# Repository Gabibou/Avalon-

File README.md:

# 🚀 Avalon

Welcome to the **Avalon Project** GitHub page!

Avalon is an open-source autonomous UAV (Unmanned Aerial Vehicle) project started in **January 2023** by two electrical engineering students passionate about aerospace, embedded systems, and autonomous flight systems.

At first, we planned to build a rocket 🚀  
But since many people were already working on similar projects, we decided to take on a different challenge:

> ✈️ Designing and building a fully autonomous flying wing.

The objective of Avalon is to develop both the **hardware** and the **software** required for a low-cost, repairable, and self-flying UAV platform.

The project combines multiple engineering fields, including:

- Embedded systems
- Electronics design
- Aerodynamics
- Autonomous navigation
- Telemetry and communication
- Power management

Avalon is also a long-term learning project that allows us to experiment, improve our skills, and progressively build more advanced autonomous flight systems.

---

# 🧩 Control Board Philosophy

The Avalon control board was designed to be flexible and reusable across multiple types of autonomous vehicles.

The main objective is to support both:

- ✈️ **2-axis flying wings and aircraft**
- 🚀 **3-axis rockets and experimental vehicles**

By keeping the hardware architecture modular, the same board can be adapted to different flight configurations with only software and parameter changes.

---

# 🔌 Communication & Control Interface

The board exposes its internal configuration and control system through a **register-based interface** accessible over USB communication.

This approach allows a computer or ground station software to:

- 📊 Read real-time telemetry values
- ⚙️ Configure onboard parameters
- 🎮 Manually control the vehicle
- 💾 Upload autonomous flight settings
- 🧪 Debug and test peripherals
- 🚀 Enable autonomous flight modes

The communication system behaves similarly to a memory-mapped register interface commonly found in embedded systems.

Each register corresponds to a specific feature or data field, such as:

- REVISION_STATUS
- SYSTEM_STATUS
- PID_CONTROL
- COMMAND
- SENSOR_CONFIG
- DEBUG
- ACTUATOR_CONFIG
- FLIGHT_CONTROL
- ALERTS
- MEMORY_CONTROL

This architecture provides a simple and scalable way to interact with the firmware while remaining hardware-independent.

---

# 📌 Roadmap

> 🚧 This section will be completed later.

---

# 🧠 Project Architecture

The project is organized into multiple folders, each with a dedicated role:

```text
Avalon/
├── mx/            # STM32CubeMX generated peripheral configuration
├── lib/           # External libraries imported using git submodules
├── test/          # Sanity and validation tests executed before commits
├── platformio/    # PlatformIO extension configuration files
├── src/           # Main firmware source files
├── inc/           # Header files and firmware interfaces
```

## 📂 Folder Details

### `mx/`

Contains STM32 peripheral configuration generated using:

- 🧩 STM32CubeMX
- ⚙️ STM32CubeIDE

This folder is mainly used to generate initialization code for peripherals such as:

- UART
- SPI
- I2C
- Timers
- DMA
- GPIO
- etc.

---

### `lib/`

Contains external dependencies and libraries imported using **Git submodules**.

This allows the project to:

- keep dependencies separated,
- simplify updates,
- and maintain cleaner firmware code.

---

### `test/`

Contains all sanity tests and validation routines that should pass before committing changes.

These tests help ensure:

- firmware stability,
- hardware reliability,
- and regression prevention.

---

### `platformio/`

Contains the configuration files used by the **PlatformIO** extension.

PlatformIO is used for:

- project building,
- dependency management,
- flashing,
- and debugging.

---

### `src/` and `inc/`

Main firmware source and header files.

These folders contain:

- flight logic,
- drivers,
- telemetry,
- navigation,
- control algorithms,
- and all embedded application code.

---

# 🛠️ First Prototype Overview

The first prototype is based on a custom board using the:

- 🧠 STM32G474RET6 MCU

It integrates:

- 📌 BNO055 IMU
- 🌡️ BMP390 barometric pressure sensor
- 📍 L80 GPS module
- 📡 Wio-E5 telemetry module
- 🔋 Current and battery voltage monitoring
- ⚡ Additional onboard peripherals

For the aircraft itself, we decided to use a **3D printed flying wing** in order to focus first on hardware and software validation.

The selected model is:

> ✈️ **EBW-160** from Eclipson

The aircraft has a wingspan of **160 cm (5.2 ft)**, making it a fairly large platform.

## 🧱 Materials

### First prototype

- Printed using standard PLA
- Lower cost and easier to replace during testing

### Future prototype

- Planned in LW-PLA (Lightweight PLA)
- Reduced weight for improved flight performance

# 📸 Prototype V1

---

# ✈️ Second Prototype Overview

---

# 📦 Cloning the Project

This project uses **Git submodules** for external libraries.

Because of this, cloning the repository normally is **not enough** ❌

You must clone the repository recursively to automatically download all dependencies.

## ✅ Recommended Clone Command

```bash
git clone --recurse-submodules https://github.com/Gabibou/Avalon-.git
```

---

## 🔄 Updating Submodules

If you already cloned the repository without submodules, run:

```bash
git submodule update --init --recursive
```

To update all submodules later:

```bash
git submodule update --remote --recursive
```

---

# 📜 License

This project is distributed under the MIT License.

📄 [MIT License](https://choosealicense.com/licenses/mit/)

---

# 🙌 Acknowledgements

Special thanks to:

- 🌱 [Seeed Studio](https://www.seeedstudio.com/) for their partnership and support.

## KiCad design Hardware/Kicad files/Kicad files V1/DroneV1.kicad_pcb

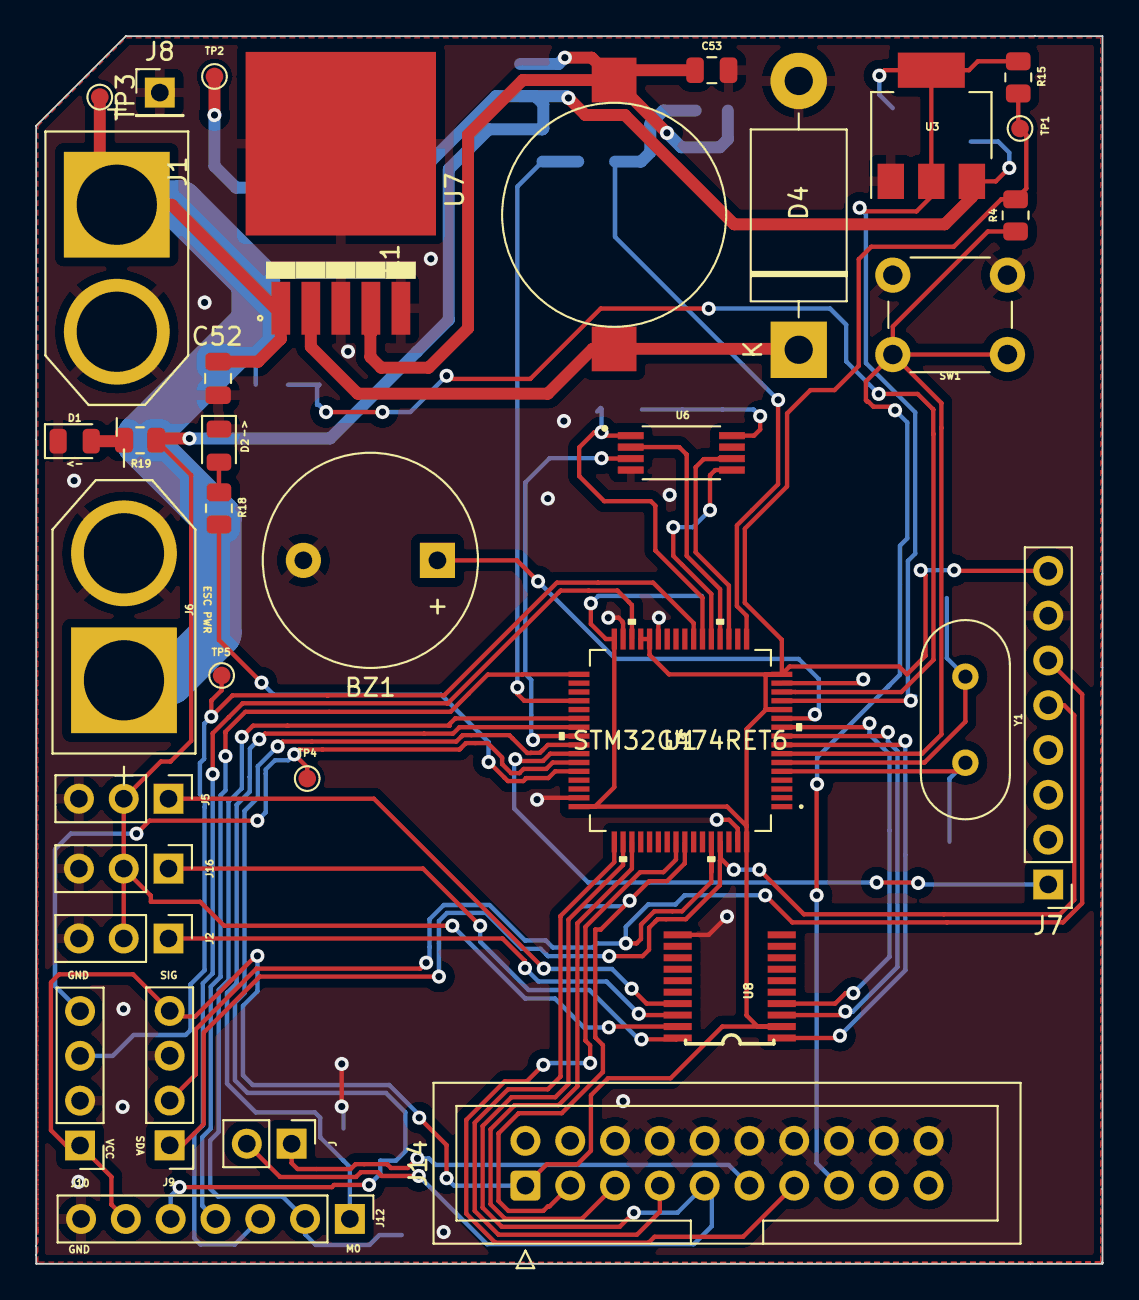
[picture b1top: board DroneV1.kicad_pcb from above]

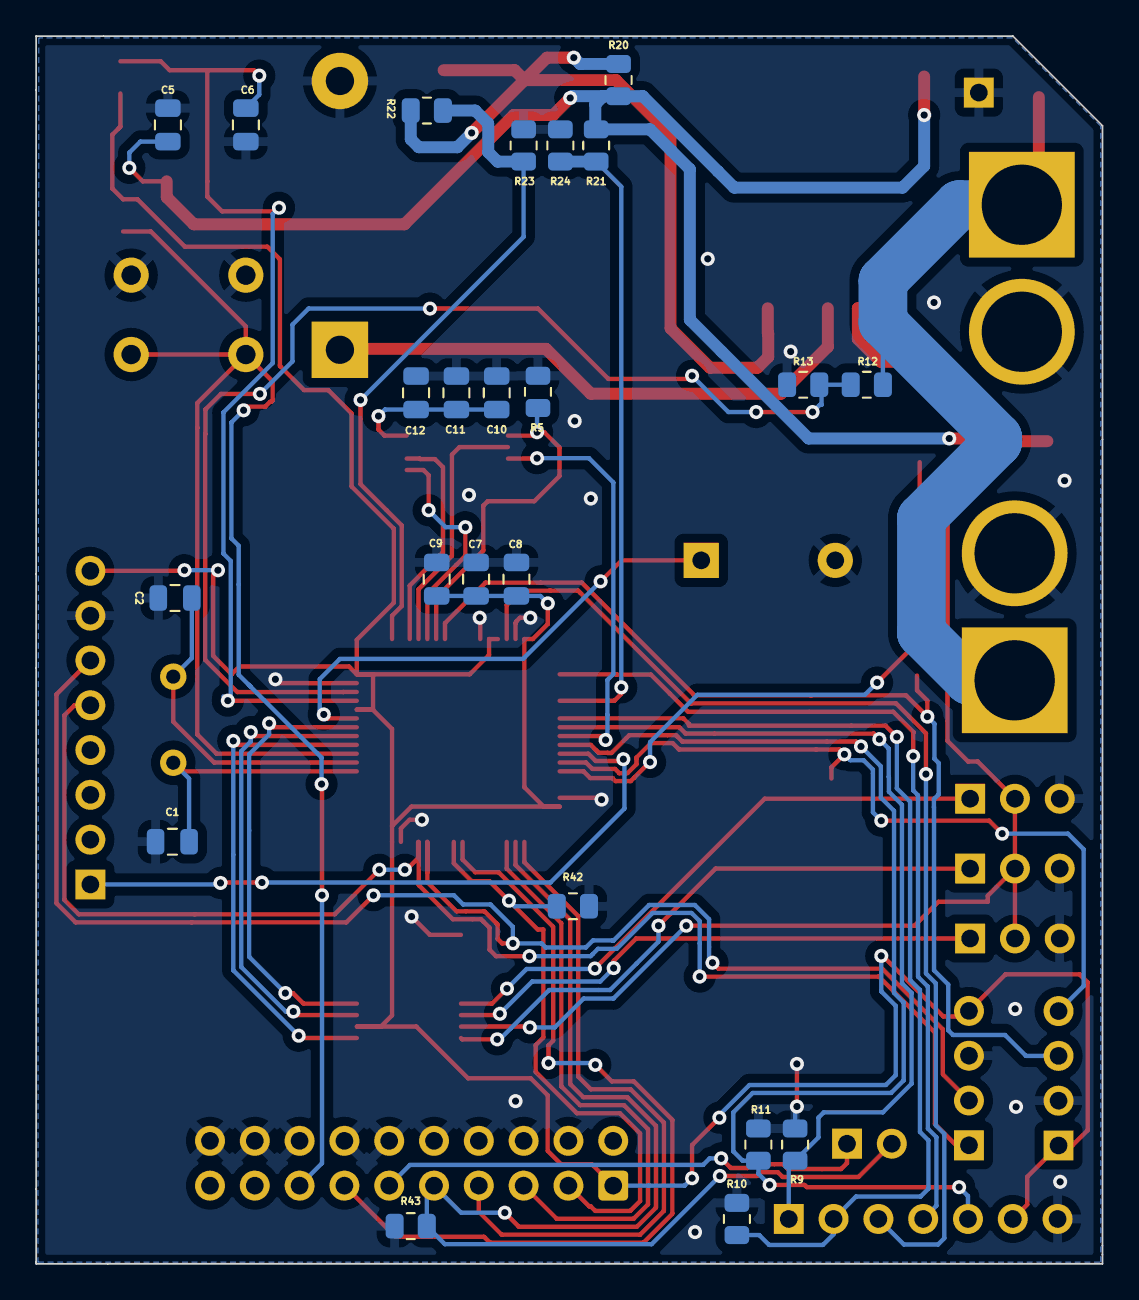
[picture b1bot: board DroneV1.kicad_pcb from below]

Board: 2 copper layers, 60.5 x 69.6 mm, 58 parts (23 on the bottom side), 44 nets.

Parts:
BZ1: Buzzer; Buzzer_12x9.5RM7.6
C1, C2, C7, C8, C9, C10, C11, C12: C_0805_2012Metric
C5, C6: 100nF; C_0805_2012Metric
C52: 100uF; C_0805_2012Metric
C53: 1000uF; C_0805_2012Metric
D1, D2: LED_0805_2012Metric
D4: 1N5822; D_DO-201AD_P15.24mm_Horizontal
J1, J6: XT60-M; AMASS_XT60-M
J2: Servo2; PinHeader_1x03_P2.54mm_Vertical
J5: ESC_control; PinHeader_1x03_P2.54mm_Vertical
J7: MPU6000; PinHeader_1x08_P2.54mm_Vertical
J8: GND; PinHeader_1x01_P2.54mm_Vertical
J9: BMP280; PinHeader_1x04_P2.54mm_Vertical
J10: PinHeader_1x04_P2.54mm_Vertical
J12: PinHeader_1x07_P2.54mm_Vertical
J14: IDC-Header_2x10_P2.54mm_Vertical
J16: Servo1; PinHeader_1x03_P2.54mm_Vertical
J : PinHeader_1x02_P2.54mm_Vertical
L1: 100uH; MP002808
R4: 100k; R_0805_2012Metric
R5, R9, R10, R11, R12, R13, R18, R42, R43: R_0805_2012Metric
R15, R20: 1; R_0805_2012Metric
R19: 10000; R_0805_2012Metric
R21, R22, R23, R24: 1000; R_0805_2012Metric
SW1: SW_Push; SW_PUSH_6mm
TP1: 3.3V TP; TestPoint_Pad_D1.0mm
TP2: 5V TP; TestPoint_Pad_D1.0mm
TP3, TP5: TestPoint_Pad_D1.0mm
TP4: TX TP; TestPoint_Pad_D1.0mm
U1: STM32G474RET6
U3: AMS1117-3.3; SOT-223-3_TabPin2
U6: SOP65P640X120-8N
U7: LM2576D2TR4-5G; D2PAK-5
U8: TXS0108E; TSSOP20
Y1: 16Mhz; Crystal_HC49-U_Vertical

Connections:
+5V: C5.1, J2.2, J5.2, J16.2, R19.1, R20.2, R21.1, TP2.1, U3.3 (VI), U8.19 (VCCB)
ADC1_IN1: C7.1, C8.1, C9.1, C10.1, C11.1, C12.1, J7.8, J9.4, J10.1, J12.6, J14.1 (VTREF), R4.2, R15.2, TP1.1, U1.12 (PA0), U1.16 (VDD), U1.28 (VREF+), U1.29 (VDDA), U1.32 (VDD), U1.48 (VDD), U1.64 (VDD), U6.8 (VCC), U8.2 (VCCA)
ADC1_IN2: C6.1, R15.1, U1.13 (PA1), U3.2 (VO)
ADC1_IN3: R12.2, R13.2, U1.14 (PA2)
ADC1_IN4: R22.2, R23.2, U1.17 (PA3)
ADC1_IN5: R21.2, R24.1, U1.36 (PB14)
Buzzer: BZ1.1 (-), U1.11 (PC3)
CS_Memory: R5.2, U1.22 (PC4), U6.1 (~CS)
GND: BZ1.2 (+), C1.1, C2.1, C5.2, C6.2, C7.2, C8.2, C9.2, C10.2, C11.2, C12.2, C52.2, C53.2, D1.1 (K), D2.1 (K), D4.2 (A), J1.N (NEG), J2.3, J5.3, J6.N (NEG), J7.7, J8.1, J9.3, J10.2, J12.7, J14.4 (GND), J14.6 (GND), J14.8 (GND), J14.10 (GND), J14.12 (GND), J14.14 (GND), J14.16 (GND), J14.18 (GND), J14.20 (GND), J16.3, R5.1, R9.2, R10.2, R11.1, R13.1, R23.1, R24.2, R42.2, R43.1, SW1.2, U1.15 (VSS), U1.27 (VSSA), U1.31 (VSS), U1.47 (VSS), U1.63 (VSS), U3.1 (GND), U6.4 (GND), U7.3 (GND), U7.5 (ON/OFF), U7.6 (GND), U8.11 (GND)
I2C_SCL: J7.6, J9.2, U1.60 (PB7)
I2C_SDA: J7.5, J9.1, U1.61 (PB8-BOOT0)
JRST: J14.3 (~TRST), R42.1, U1.57 (PB4)
JTCK: J14.9 (TCK/SWDCLK), J.2, R43.2, U1.50 (PA14)
JTDI: J14.5 (TDI), U1.51 (PA15)
JTDO: J14.13 (TDO/SWO), U1.56 (PB3)
JTMS: J14.7 (TMS/SWDIO), U1.49 (PA13)
LD1: R18.1, U1.44 (PA10)
Lora_Aux: J12.5, R11.2, U1.41 (PC9)
Lora_M0: J12.1, R9.1, U1.39 (PC7)
Lora_M1: J12.2, R10.1, U1.38 (PC6)
MPU6000_IT: J7.1, U1.42 (PA8)
unnamed: C53.1, L1.2, R20.1, R22.1, U7.4 (FB)
unnamed: D1.2 (A), R19.2
unnamed: D2.2 (A), R18.2
unnamed: D4.1 (K), L1.1, U7.2 (OUT)
unnamed: J14.11 (RTCK), J.1
PWM_BRUSHLESS_3.3V: U1.10 (PC2), U8.4 (A3)
PWM_BRUSHLESS_5V: J5.1, U8.17 (B3)
PWM_SERVO1_3.3V: U1.8 (PC0), U8.1 (A1)
PWM_SERVO1_5V: J16.1, U8.20 (B1)
PWM_SERVO2_3.3V: U1.9 (PC1), U8.3 (A2)
PWM_SERVO2_5V: J2.1, U8.18 (B2)
Qin: C1.2, U1.5 (PF0-OSC_IN), Y1.2
Qout: C2.2, U1.6 (PF1-OSC_OUT), Y1.1
RESET MCU: J14.15 (~SRST), R4.1, SW1.1, U1.7 (PG10-NRST)
SPICLK: U1.19 (PA5), U6.6 (SCK)
SPI_MISO: U1.20 (PA6), U6.2 (SO(I/O1))
SPI_MOSI: U1.21 (PA7), U6.5 (SI(I/O0))
UART1_RX: J10.3, TP5.1, U1.23 (PC5)
UART1_TX: J10.4, TP4.1, U1.43 (PA9)
UART3_RX: J12.4, U1.33 (PB11)
UART3_TX: J12.3, U1.30 (PB10)
VBAT: C52.1, J1.P (POS), J6.P (POS), R12.1, TP3.1, U7.1 (VIN)
WP_Memory: U1.40 (PC8), U6.3 (~WP)

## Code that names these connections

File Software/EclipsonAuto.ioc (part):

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Mcu.Name=STM32G474R(B-C-E)Tx
Mcu.Package=LQFP64
Mcu.UserName=STM32G474RETx
PA10.GPIOParameters=GPIO_Label
PA10.GPIO_Label=LD1
PA10.Signal=GPIO_Output
PA13.Mode=Trace_Asynchronous_SW
PA13.Signal=SYS_JTMS-SWDIO
PA14.Mode=Trace_Asynchronous_SW
PA14.Signal=SYS_JTCK-SWCLK
PA2.Mode=IN3-Single-Ended
PA2.Signal=ADC1_IN3
PA3.Mode=IN4-Single-Ended
PA3.Signal=ADC1_IN4
PA5.GPIOParameters=GPIO_PuPd
PA5.GPIO_PuPd=GPIO_NOPULL
PA5.Mode=Full_Duplex_Master
PA5.Signal=SPI1_SCK
PA6.GPIOParameters=GPIO_PuPd
PA6.GPIO_PuPd=GPIO_NOPULL
PA6.Mode=Full_Duplex_Master
PA6.Signal=SPI1_MISO
PA7.GPIOParameters=GPIO_PuPd
PA7.GPIO_PuPd=GPIO_NOPULL
PA7.Mode=Full_Duplex_Master
PA7.Signal=SPI1_MOSI
PB14.Signal=SharedAnalog_PB14
PB3.Mode=Trace_Asynchronous_SW
PB3.Signal=SYS_JTDO-SWO
PB7.Mode=I2C
PB7.Signal=I2C1_SDA
PB8-BOOT0.Mode=I2C
PB8-BOOT0.Signal=I2C1_SCL
PC0.GPIOParameters=GPIO_ModeDefaultPP,GPIO_Label
PC0.GPIO_Label=SERVO1_PWM
PC0.GPIO_ModeDefaultPP=GPIO_MODE_AF_OD
PC0.Signal=S_TIM1_CH1
PC1.GPIOParameters=GPIO_ModeDefaultPP,GPIO_Label
PC1.GPIO_Label=SERVO2_PWM
PC1.GPIO_ModeDefaultPP=GPIO_MODE_AF_OD
PC1.Signal=S_TIM1_CH2
PC2.GPIOParameters=GPIO_ModeDefaultPP,GPIO_Label
PC2.GPIO_Label=ESC_PWM
PC2.GPIO_ModeDefaultPP=GPIO_MODE_AF_OD
PC2.Signal=S_TIM1_CH3
PC4.GPIOParameters=GPIO_PuPd,GPIO_Label
PC4.GPIO_Label=CS_Memory
PC4.GPIO_PuPd=GPIO_PULLDOWN
PC4.Signal=GPIO_Output
RCC.HSE_VALUE=8000000
RCC.SYSCLKFreq_VALUE=150000000
RCC.SYSCLKSource=RCC_SYSCLKSOURCE_PLLCLK
board=custom

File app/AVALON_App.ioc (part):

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Mcu.Name=STM32G474R(B-C-E)Tx
Mcu.Package=LQFP64
Mcu.UserName=STM32G474RETx
PA0.Mode=IN1-Differential
PA0.Signal=ADC2_IN1
PA1.Mode=IN1-Differential
PA1.Signal=ADC2_IN2
PA10.GPIOParameters=GPIO_Label
PA10.GPIO_Label=IMU_IT
PA10.Signal=GPXTI10
PA5.Mode=Full_Duplex_Master
PA5.Signal=SPI1_SCK
PA6.Mode=Full_Duplex_Master
PA6.Signal=SPI1_MISO
PA7.Mode=Full_Duplex_Master
PA7.Signal=SPI1_MOSI
PA9.GPIOParameters=GPIO_Label
PA9.GPIO_Label=LED
PA9.Signal=GPIO_Output
PB6.Signal=S_TIM4_CH1
PB7.Signal=S_TIM4_CH2
PB9.Signal=S_TIM4_CH4
PC0.Mode=IN6-Differential
PC0.Signal=ADC2_IN6
PC1.Mode=IN6-Differential
PC1.Signal=ADC2_IN7
PC10.Mode=Asynchronous
PC10.Signal=UART4_TX
PC11.Mode=Asynchronous
PC11.Signal=UART4_RX
PC12.Mode=Asynchronous
PC12.Signal=UART5_TX
PC4.Mode=I2C
PC4.Signal=I2C2_SCL
PC6.Signal=S_TIM3_CH1
PD2.Mode=Asynchronous
PD2.Signal=UART5_RX
PF0-OSC_IN.Mode=I2C
PF0-OSC_IN.Signal=I2C2_SDA
PF1-OSC_OUT.Mode=IN10-Single-Ended
PF1-OSC_OUT.Signal=ADC2_IN10
RCC.HSE_VALUE=8000000
RCC.SYSCLKFreq_VALUE=150000000
RCC.SYSCLKSource=RCC_SYSCLKSOURCE_PLLCLK
board=custom

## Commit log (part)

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2023-02-15 Hardware board V1
    Added some board ( Gerber and Kicad ) files.
    This board is use only as a dev board and shouldn't be use as a functional board. It embed a 4Mb memory , GPS/IMU/Lora emitter/ESC and pwm control/BMP280 barometric sensor.
2023-02-15 Software folder creation
    Added STM32Cube IDE project
    Added the classic Hello World (Flashing led)
    Added Voltage measurement and current measurement
2023-02-15 Patch bug
    File is a .zip file sorry ;D
2023-02-19 Added MPU6050 own library
    This small lib allow the user to get data from the sensors + select low power mode or wake up mode + select cycle mode and his configuration + config interupt and enable interupt
2023-02-26 Update begin
2023-02-26 Added AT25XV041B flash driver
2023-03-11 Update incoming
2023-03-11 Patch on the 4Mb flash memory lib
    Patched the lib + full set of function now available
2023-03-18 Flash lib update
    Flash lib update with 2 new function :
    - Writing a coordinate into the memory
    -reading this coordinate from the memory
    Also added a few test on motor control
2023-03-25 pre update
2023-03-25 Added motor control using timer 1
    In a future update, the highres timer will be use
2023-03-31 Added a schematic for board V2.0
2023-04-01 Added schematic for board V2 (PowerPoint Version)
2023-04-02 Reorganized folders
2023-04-02 Added Schematic for board V2
2023-04-02 Added gerber files for V1/V2 board
2023-04-02 Added board V2 schematic + kicad files
2023-04-02 Added kicad files version1
2023-04-09 PreUpdate
2023-04-09 Try to add all project #1
2023-04-09 Added PID
    Also added some files for board V2. Will be use later
2023-04-09 Added PID and much more
    PID + wio-e5 pre driver + GPS pre driver + much more
2023-04-09 Added schematic for software dev
2023-05-07 Added Bno055 driver + BMP390 driver + Wioe5 driver + Update comment
2023-05-10 Update README.md
    Added picture PCB V1
2023-05-13 Change pinout for board V2
    Also added BIST and self power test for IMU
2023-10-30 Delete Hardware directory
    Rework git repo
2023-10-30 Update avalon software
    Split the software into two project : Bootloader | Application
2023-10-30 Revert "Software"
2023-10-30 Revert "Software" (#12)
2023-10-30 Begining of V2.0
    Split firmware into two section Bootloader | App
2023-11-09 reshape Avalon project
2023-11-09 Minor Millestone - TaskCreation
2023-11-17 Update GPS IT
2023-11-17 GPS fully integrated
2023-11-20 tools creation + esc skywalker setup software
2023-11-25 ESC & Thruster test + new startup procedure + Bugfix
2023-11-30 IMU drivers update + High G threshold set
2023-12-11 HIGH G integration OK - need to check calibration
2023-12-16 Launch procedure rework
2023-12-23 IMU drivers upgrade
2023-12-27 BugFixDelay at startup
2024-01-01 Add external flash drivers + first IMU speed calculation test + wioe5 drivers
2024-01-20 WIOE5 driver started
2024-01-26 git clean + bootloader reactivated
2024-01-26 Git cleanup
2024-01-26 Wioe5 driver update
2024-01-28 update lora driver
2024-01-28 driver WIOE5 update
2024-02-01 Driver update wioE5
2024-02-15 Bootloader atempt V0.1
2024-02-23 Bootloader rework - Not fully tested yet
2024-03-09 Bootloader update
2024-03-09 Bootloader OK,app crash in init
2026-04-23 [UPDATE] - initial commit for project refacto
2026-04-23 [UPDATE] - removed tools, app and bootloader from project
2026-04-25 [UPDATE] - imported as submodules bno055 library
2026-04-25 [UPDATE] - include bosh bmp third generation library submodule
2026-04-25 [BUGFIX] - fixed bno055 submodule import
2026-04-27 [UPDATE] - added imu boot method and generated ui file
2026-04-27 [UPDATE] - added user interface basics
2026-05-11 [UPDATE] - Added USB Virtual Com Port + Added user interface init method
2026-05-14 [UPDATE] - Update README.md

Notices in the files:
parts and their libraries:
Copyright 2021 Accelerated Designs. All rights reserved.
